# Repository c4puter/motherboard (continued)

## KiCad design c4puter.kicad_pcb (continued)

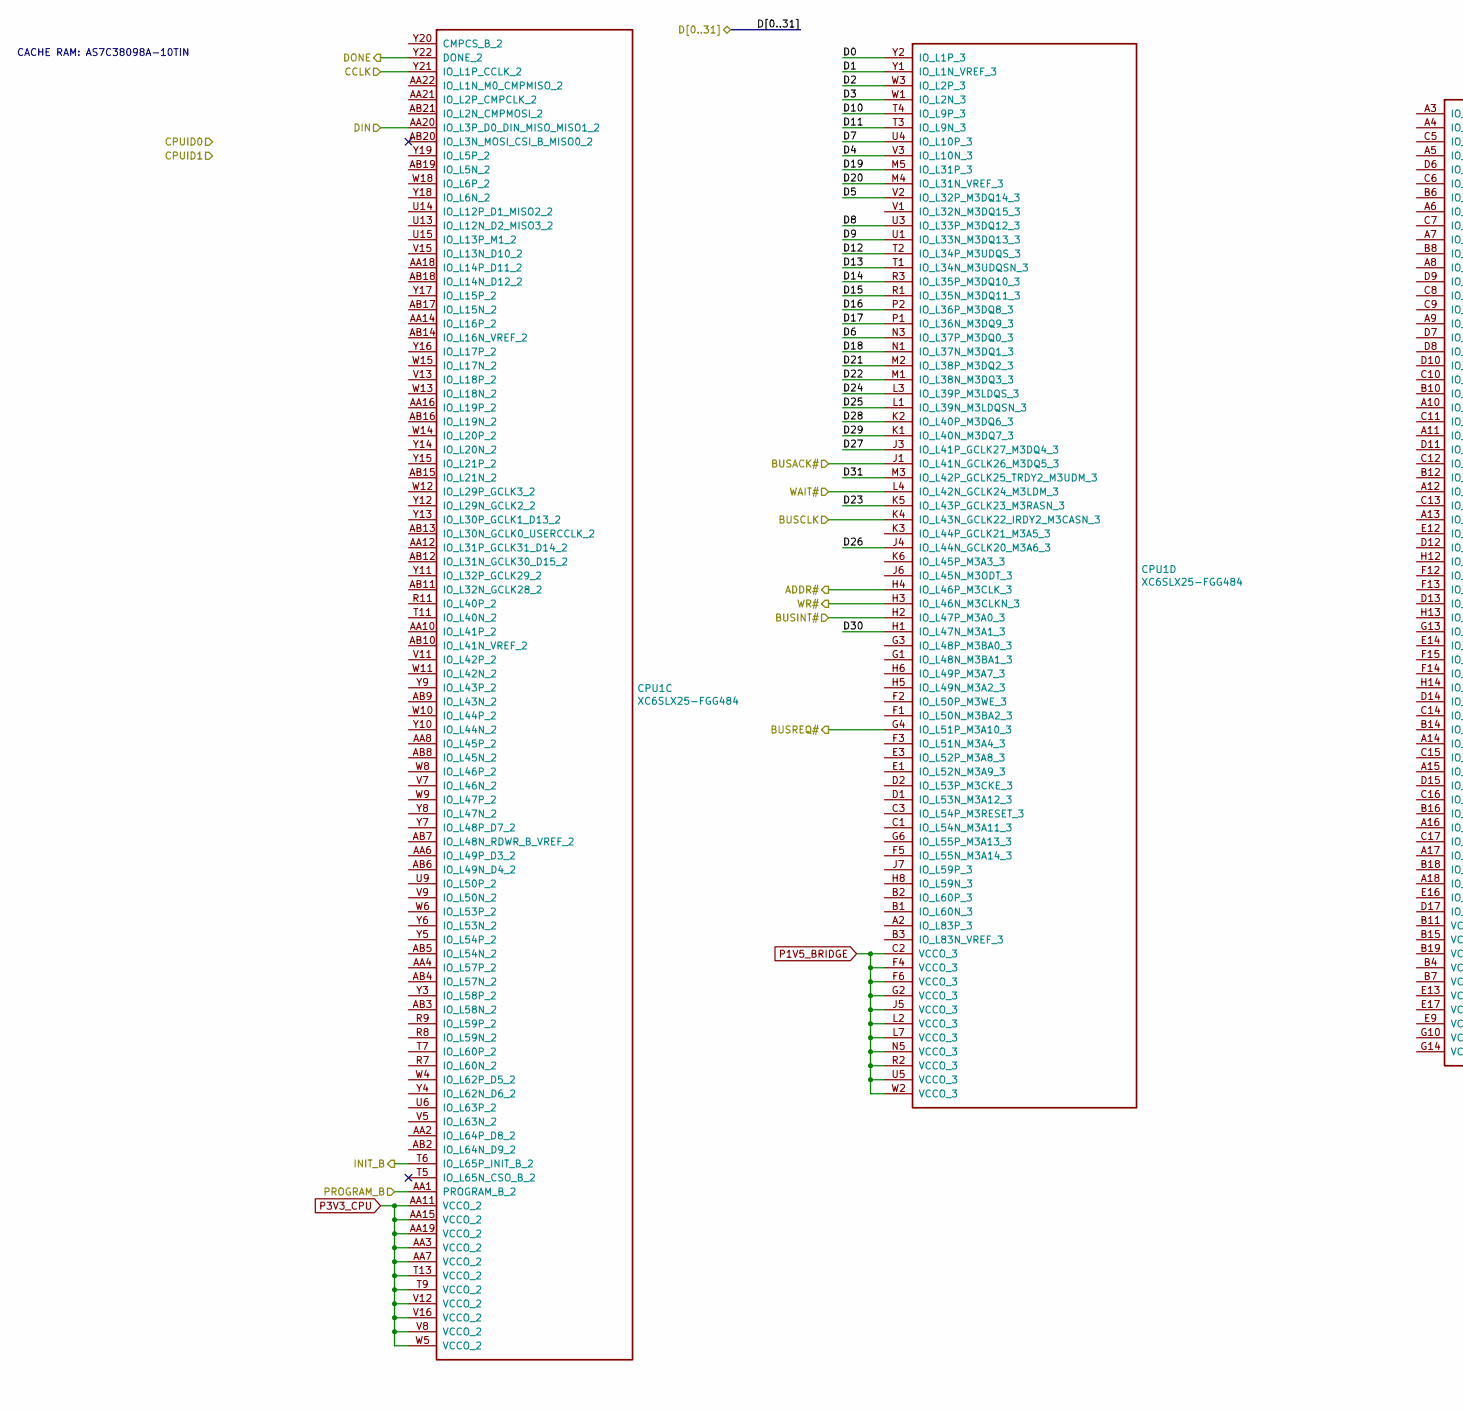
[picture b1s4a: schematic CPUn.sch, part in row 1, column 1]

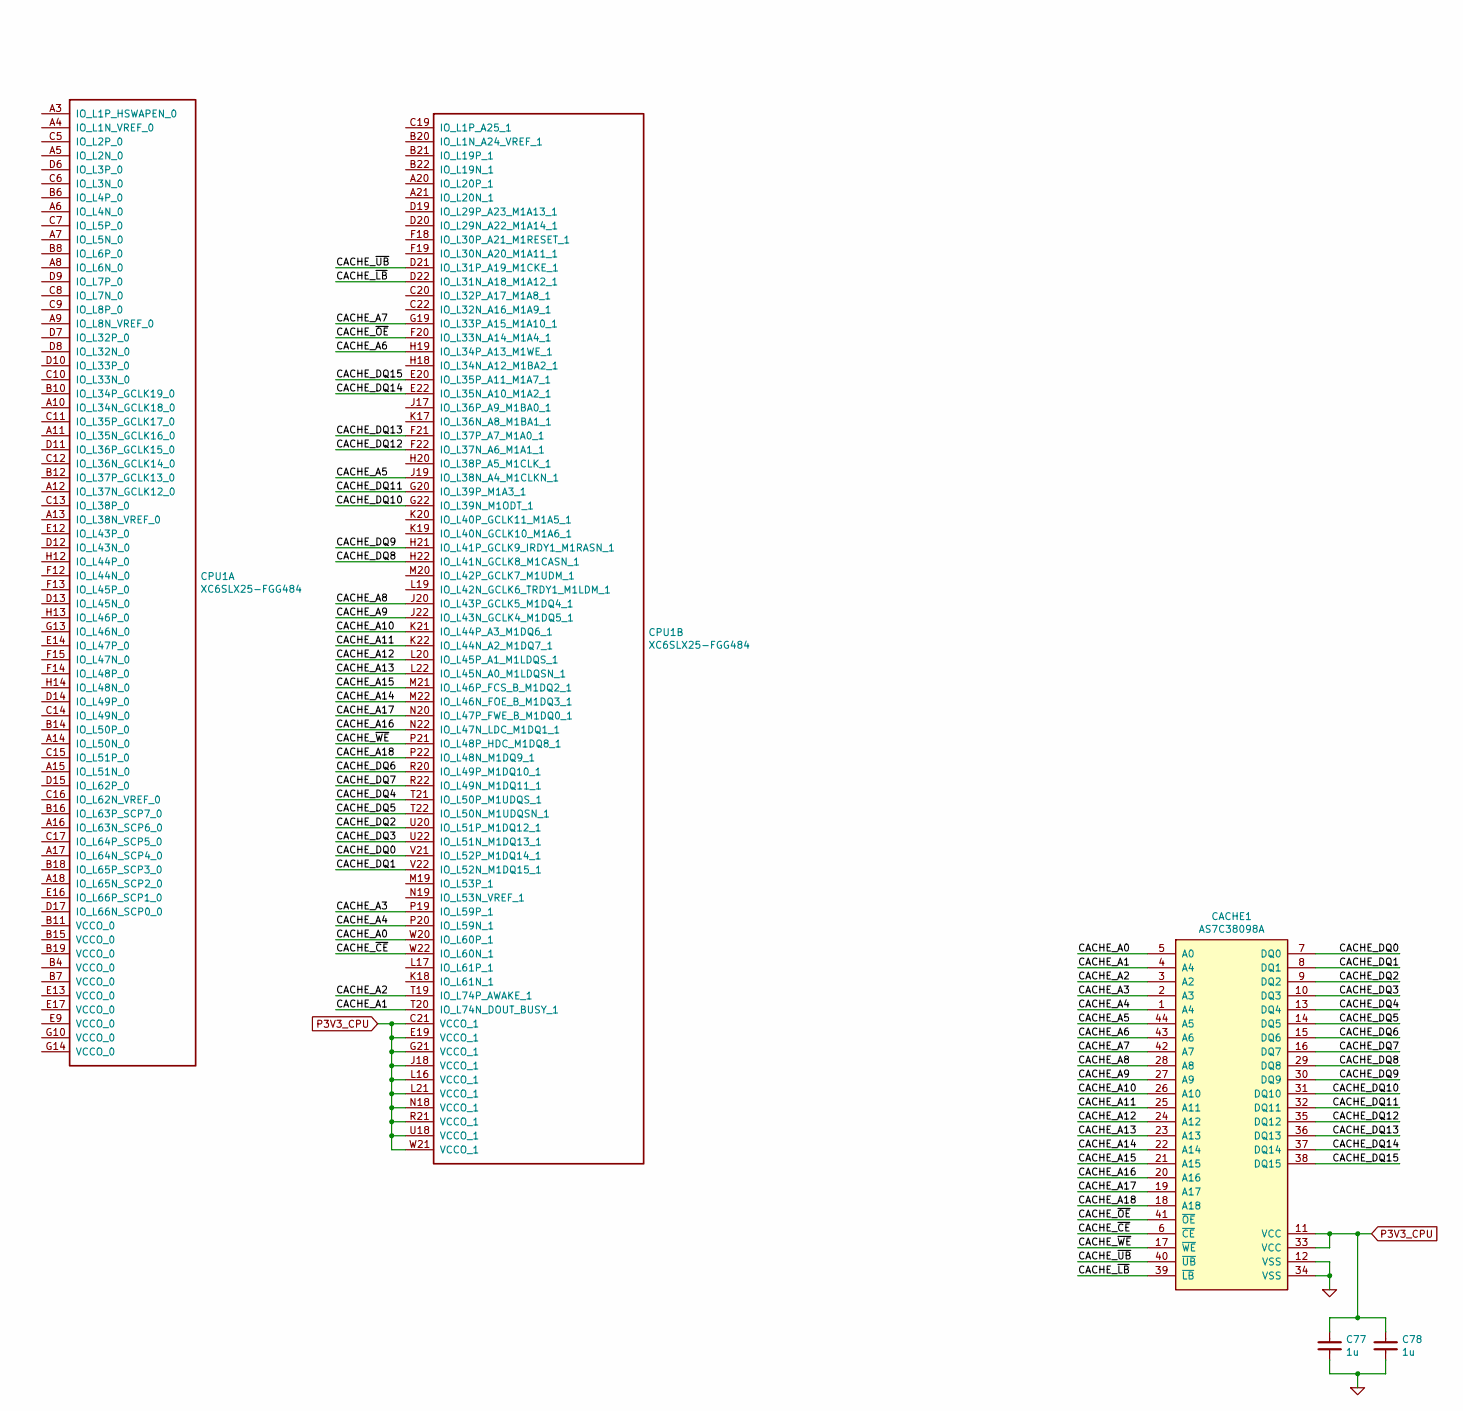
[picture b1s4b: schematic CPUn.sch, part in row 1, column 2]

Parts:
C75, C76: 1u; CAPC1005X55
CACHE0: AS7C38098A; SOP80P1176X120-44
CPU0: XC6SLX25-FGG484; XILINX-FGG484

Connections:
/CPU0/ADDR#: CPU0.H4 (IO_L46P_M3CLK_3); also elsewhere on the board
/CPU0/BUSACK#: CPU0.J1 (IO_L41N_GCLK26_M3DQ5_3); also elsewhere on the board
/CPU0/BUSCLK: CPU0.K4 (IO_L43N_GCLK22_IRDY2_M3CASN_3); also elsewhere on the board
/CPU0/BUSINT#: CPU0.H2 (IO_L47P_M3A0_3); also elsewhere on the board
/CPU0/BUSREQ#: CPU0.G4 (IO_L51P_M3A10_3); also elsewhere on the board
/CPU0/CACHE_A0: CACHE0.5 (A0), CPU0.W20 (IO_L60P_1)
/CPU0/CACHE_A1: CACHE0.4 (A4), CPU0.T20 (IO_L74N_DOUT_BUSY_1)
/CPU0/CACHE_A2: CACHE0.3 (A2), CPU0.T19 (IO_L74P_AWAKE_1)
/CPU0/CACHE_A3: CACHE0.2 (A3), CPU0.P19 (IO_L59P_1)
/CPU0/CACHE_A4: CACHE0.1 (A4), CPU0.P20 (IO_L59N_1)
/CPU0/CACHE_A5: CACHE0.44 (A5), CPU0.J19 (IO_L38N_A4_M1CLKN_1)
/CPU0/CACHE_A6: CACHE0.43 (A6), CPU0.H19 (IO_L34P_A13_M1WE_1)
/CPU0/CACHE_A7: CACHE0.42 (A7), CPU0.G19 (IO_L33P_A15_M1A10_1)
/CPU0/CACHE_A8: CACHE0.28 (A8), CPU0.J20 (IO_L43P_GCLK5_M1DQ4_1)
/CPU0/CACHE_A9: CACHE0.27 (A9), CPU0.J22 (IO_L43N_GCLK4_M1DQ5_1)
/CPU0/CACHE_A10: CACHE0.26 (A10), CPU0.K21 (IO_L44P_A3_M1DQ6_1)
/CPU0/CACHE_A11: CACHE0.25 (A11), CPU0.K22 (IO_L44N_A2_M1DQ7_1)
/CPU0/CACHE_A12: CACHE0.24 (A12), CPU0.L20 (IO_L45P_A1_M1LDQS_1)
/CPU0/CACHE_A13: CACHE0.23 (A13), CPU0.L22 (IO_L45N_A0_M1LDQSN_1)
/CPU0/CACHE_A14: CACHE0.22 (A14), CPU0.M22 (IO_L46N_FOE_B_M1DQ3_1)
/CPU0/CACHE_A15: CACHE0.21 (A15), CPU0.M21 (IO_L46P_FCS_B_M1DQ2_1)
/CPU0/CACHE_A16: CACHE0.20 (A16), CPU0.N22 (IO_L47N_LDC_M1DQ1_1)
/CPU0/CACHE_A17: CACHE0.19 (A17), CPU0.N20 (IO_L47P_FWE_B_M1DQ0_1)
/CPU0/CACHE_A18: CACHE0.18 (A18), CPU0.P22 (IO_L48N_M1DQ9_1)
/CPU0/CACHE_DQ0: CACHE0.7 (DQ0), CPU0.V21 (IO_L52P_M1DQ14_1)
/CPU0/CACHE_DQ1: CACHE0.8 (DQ1), CPU0.V22 (IO_L52N_M1DQ15_1)
/CPU0/CACHE_DQ2: CACHE0.9 (DQ2), CPU0.U20 (IO_L51P_M1DQ12_1)
/CPU0/CACHE_DQ3: CACHE0.10 (DQ3), CPU0.U22 (IO_L51N_M1DQ13_1)
/CPU0/CACHE_DQ4: CACHE0.13 (DQ4), CPU0.T21 (IO_L50P_M1UDQS_1)
/CPU0/CACHE_DQ5: CACHE0.14 (DQ5), CPU0.T22 (IO_L50N_M1UDQSN_1)
/CPU0/CACHE_DQ6: CACHE0.15 (DQ6), CPU0.R20 (IO_L49P_M1DQ10_1)
/CPU0/CACHE_DQ7: CACHE0.16 (DQ7), CPU0.R22 (IO_L49N_M1DQ11_1)
/CPU0/CACHE_DQ8: CACHE0.29 (DQ8), CPU0.H22 (IO_L41N_GCLK8_M1CASN_1)
/CPU0/CACHE_DQ9: CACHE0.30 (DQ9), CPU0.H21 (IO_L41P_GCLK9_IRDY1_M1RASN_1)
/CPU0/CACHE_DQ10: CACHE0.31 (DQ10), CPU0.G22 (IO_L39N_M1ODT_1)
/CPU0/CACHE_DQ11: CACHE0.32 (DQ11), CPU0.G20 (IO_L39P_M1A3_1)
/CPU0/CACHE_DQ12: CACHE0.35 (DQ12), CPU0.F22 (IO_L37N_A6_M1A1_1)
/CPU0/CACHE_DQ13: CACHE0.36 (DQ13), CPU0.F21 (IO_L37P_A7_M1A0_1)
/CPU0/CACHE_DQ14: CACHE0.37 (DQ14), CPU0.E22 (IO_L35N_A10_M1A2_1)
/CPU0/CACHE_DQ15: CACHE0.38 (DQ15), CPU0.E20 (IO_L35P_A11_M1A7_1)
/CPU0/CACHE_~CE: CACHE0.6 (~CE), CPU0.W22 (IO_L60N_1)
/CPU0/CACHE_~LB: CACHE0.39 (~LB), CPU0.D22 (IO_L31N_A18_M1A12_1)
/CPU0/CACHE_~OE: CACHE0.41 (~OE), CPU0.F20 (IO_L33N_A14_M1A4_1)
/CPU0/CACHE_~UB: CACHE0.40 (~UB), CPU0.D21 (IO_L31P_A19_M1CKE_1)
/CPU0/CACHE_~WE: CACHE0.17 (~WE), CPU0.P21 (IO_L48P_HDC_M1DQ8_1)
/CPU0/CCLK: CPU0.Y21 (IO_L1P_CCLK_2); also elsewhere on the board
/CPU0/DIN: CPU0.AA20 (IO_L3P_D0_DIN_MISO_MISO1_2); also elsewhere on the board
/CPU0/DONE: CPU0.Y22 (DONE_2); also elsewhere on the board
/CPU0/INIT_B: CPU0.T6 (IO_L65P_INIT_B_2); also elsewhere on the board
/CPU0/PROGRAM_B: CPU0.AA1 (PROGRAM_B_2); also elsewhere on the board
/Multibridge/CPU_D0: CPU0.Y2 (IO_L1P_3); also elsewhere on the board
/Multibridge/CPU_D1: CPU0.Y1 (IO_L1N_VREF_3); also elsewhere on the board
/Multibridge/CPU_D2: CPU0.W3 (IO_L2P_3); also elsewhere on the board
/Multibridge/CPU_D3: CPU0.W1 (IO_L2N_3); also elsewhere on the board
/Multibridge/CPU_D4: CPU0.V3 (IO_L10N_3); also elsewhere on the board
/Multibridge/CPU_D5: CPU0.V2 (IO_L32P_M3DQ14_3); also elsewhere on the board
/Multibridge/CPU_D6: CPU0.N3 (IO_L37P_M3DQ0_3); also elsewhere on the board
/Multibridge/CPU_D7: CPU0.U4 (IO_L10P_3); also elsewhere on the board
/Multibridge/CPU_D8: CPU0.U3 (IO_L33P_M3DQ12_3); also elsewhere on the board
/Multibridge/CPU_D9: CPU0.U1 (IO_L33N_M3DQ13_3); also elsewhere on the board
/Multibridge/CPU_D10: CPU0.T4 (IO_L9P_3); also elsewhere on the board
/Multibridge/CPU_D11: CPU0.T3 (IO_L9N_3); also elsewhere on the board
/Multibridge/CPU_D12: CPU0.T2 (IO_L34P_M3UDQS_3); also elsewhere on the board
/Multibridge/CPU_D13: CPU0.T1 (IO_L34N_M3UDQSN_3); also elsewhere on the board
/Multibridge/CPU_D14: CPU0.R3 (IO_L35P_M3DQ10_3); also elsewhere on the board
/Multibridge/CPU_D15: CPU0.R1 (IO_L35N_M3DQ11_3); also elsewhere on the board
/Multibridge/CPU_D16: CPU0.P2 (IO_L36P_M3DQ8_3); also elsewhere on the board
/Multibridge/CPU_D17: CPU0.P1 (IO_L36N_M3DQ9_3); also elsewhere on the board
/Multibridge/CPU_D18: CPU0.N1 (IO_L37N_M3DQ1_3); also elsewhere on the board
/Multibridge/CPU_D19: CPU0.M5 (IO_L31P_3); also elsewhere on the board
/Multibridge/CPU_D20: CPU0.M4 (IO_L31N_VREF_3); also elsewhere on the board
/Multibridge/CPU_D21: CPU0.M2 (IO_L38P_M3DQ2_3); also elsewhere on the board
/Multibridge/CPU_D22: CPU0.M1 (IO_L38N_M3DQ3_3); also elsewhere on the board
/Multibridge/CPU_D23: CPU0.K5 (IO_L43P_GCLK23_M3RASN_3); also elsewhere on the board
/Multibridge/CPU_D24: CPU0.L3 (IO_L39P_M3LDQS_3); also elsewhere on the board
/Multibridge/CPU_D25: CPU0.L1 (IO_L39N_M3LDQSN_3); also elsewhere on the board
/Multibridge/CPU_D26: CPU0.J4 (IO_L44N_GCLK20_M3A6_3); also elsewhere on the board
/Multibridge/CPU_D27: CPU0.J3 (IO_L41P_GCLK27_M3DQ4_3); also elsewhere on the board
/Multibridge/CPU_D28: CPU0.K2 (IO_L40P_M3DQ6_3); also elsewhere on the board
/Multibridge/CPU_D29: CPU0.K1 (IO_L40N_M3DQ7_3); also elsewhere on the board
/Multibridge/CPU_D30: CPU0.H1 (IO_L47N_M3A1_3); also elsewhere on the board
/Multibridge/CPU_D31: CPU0.M3 (IO_L42P_GCLK25_TRDY2_M3UDM_3); also elsewhere on the board
/Multibridge/CPU_WAIT#: CPU0.L4 (IO_L42N_GCLK24_M3LDM_3); also elsewhere on the board
/Multibridge/CPU_WR#: CPU0.H3 (IO_L46N_M3CLKN_3); also elsewhere on the board
GND: C75.2, C76.2, CACHE0.12 (VSS), CACHE0.34 (VSS); also elsewhere on the board
P1V5_BRIDGE: CPU0.C2 (VCCO_3), CPU0.F4 (VCCO_3), CPU0.F6 (VCCO_3), CPU0.G2 (VCCO_3), CPU0.J5 (VCCO_3), CPU0.L2 (VCCO_3), CPU0.L7 (VCCO_3), CPU0.N5 (VCCO_3), CPU0.R2 (VCCO_3), CPU0.U5 (VCCO_3), CPU0.W2 (VCCO_3); also elsewhere on the board
P3V3_CPU: C75.1, C76.1, CACHE0.11 (VCC), CACHE0.33 (VCC), CPU0.AA3 (VCCO_2), CPU0.AA7 (VCCO_2), CPU0.AA11 (VCCO_2), CPU0.AA15 (VCCO_2), CPU0.AA19 (VCCO_2), CPU0.C21 (VCCO_1), CPU0.E19 (VCCO_1), CPU0.G21 (VCCO_1), CPU0.J18 (VCCO_1), CPU0.L16 (VCCO_1), CPU0.L21 (VCCO_1), CPU0.N18 (VCCO_1), CPU0.R21 (VCCO_1), CPU0.T9 (VCCO_2), CPU0.T13 (VCCO_2), CPU0.U18 (VCCO_1), CPU0.V8 (VCCO_2), CPU0.V12 (VCCO_2), CPU0.V16 (VCCO_2), CPU0.W5 (VCCO_2), CPU0.W21 (VCCO_1); also elsewhere on the board

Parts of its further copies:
C77, C78: 1u; CAPC1005X55
CACHE1: AS7C38098A; SOP80P1176X120-44

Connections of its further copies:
/CPU1/CACHE_A0: CACHE1.5 (A0); also elsewhere on the board
/CPU1/CACHE_A1: CACHE1.4 (A4); also elsewhere on the board
/CPU1/CACHE_A2: CACHE1.3 (A2); also elsewhere on the board
/CPU1/CACHE_A3: CACHE1.2 (A3); also elsewhere on the board
/CPU1/CACHE_A4: CACHE1.1 (A4); also elsewhere on the board
/CPU1/CACHE_A5: CACHE1.44 (A5); also elsewhere on the board
/CPU1/CACHE_A6: CACHE1.43 (A6); also elsewhere on the board
/CPU1/CACHE_A7: CACHE1.42 (A7); also elsewhere on the board
/CPU1/CACHE_A8: CACHE1.28 (A8); also elsewhere on the board
/CPU1/CACHE_A9: CACHE1.27 (A9); also elsewhere on the board
/CPU1/CACHE_A10: CACHE1.26 (A10); also elsewhere on the board
/CPU1/CACHE_A11: CACHE1.25 (A11); also elsewhere on the board
/CPU1/CACHE_A12: CACHE1.24 (A12); also elsewhere on the board
/CPU1/CACHE_A13: CACHE1.23 (A13); also elsewhere on the board
/CPU1/CACHE_A14: CACHE1.22 (A14); also elsewhere on the board
/CPU1/CACHE_A15: CACHE1.21 (A15); also elsewhere on the board
/CPU1/CACHE_A16: CACHE1.20 (A16); also elsewhere on the board
/CPU1/CACHE_A17: CACHE1.19 (A17); also elsewhere on the board
/CPU1/CACHE_A18: CACHE1.18 (A18); also elsewhere on the board
/CPU1/CACHE_DQ0: CACHE1.7 (DQ0); also elsewhere on the board
/CPU1/CACHE_DQ1: CACHE1.8 (DQ1); also elsewhere on the board
/CPU1/CACHE_DQ2: CACHE1.9 (DQ2); also elsewhere on the board
/CPU1/CACHE_DQ3: CACHE1.10 (DQ3); also elsewhere on the board
/CPU1/CACHE_DQ4: CACHE1.13 (DQ4); also elsewhere on the board
/CPU1/CACHE_DQ5: CACHE1.14 (DQ5); also elsewhere on the board
/CPU1/CACHE_DQ6: CACHE1.15 (DQ6); also elsewhere on the board
/CPU1/CACHE_DQ7: CACHE1.16 (DQ7); also elsewhere on the board
/CPU1/CACHE_DQ8: CACHE1.29 (DQ8); also elsewhere on the board
/CPU1/CACHE_DQ9: CACHE1.30 (DQ9); also elsewhere on the board
/CPU1/CACHE_DQ10: CACHE1.31 (DQ10); also elsewhere on the board
/CPU1/CACHE_DQ11: CACHE1.32 (DQ11); also elsewhere on the board
/CPU1/CACHE_DQ12: CACHE1.35 (DQ12); also elsewhere on the board
/CPU1/CACHE_DQ13: CACHE1.36 (DQ13); also elsewhere on the board
/CPU1/CACHE_DQ14: CACHE1.37 (DQ14); also elsewhere on the board
/CPU1/CACHE_DQ15: CACHE1.38 (DQ15); also elsewhere on the board
/CPU1/CACHE_~CE: CACHE1.6 (~CE); also elsewhere on the board
/CPU1/CACHE_~LB: CACHE1.39 (~LB); also elsewhere on the board
/CPU1/CACHE_~OE: CACHE1.41 (~OE); also elsewhere on the board
/CPU1/CACHE_~UB: CACHE1.40 (~UB); also elsewhere on the board
/CPU1/CACHE_~WE: CACHE1.17 (~WE); also elsewhere on the board
GND: C77.2, C78.2, CACHE1.12 (VSS), CACHE1.34 (VSS); also elsewhere on the board
P3V3_CPU: C77.1, C78.1, CACHE1.11 (VCC), CACHE1.33 (VCC); also elsewhere on the board

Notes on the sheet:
CACHE RAM: AS7C38098A-10TIN

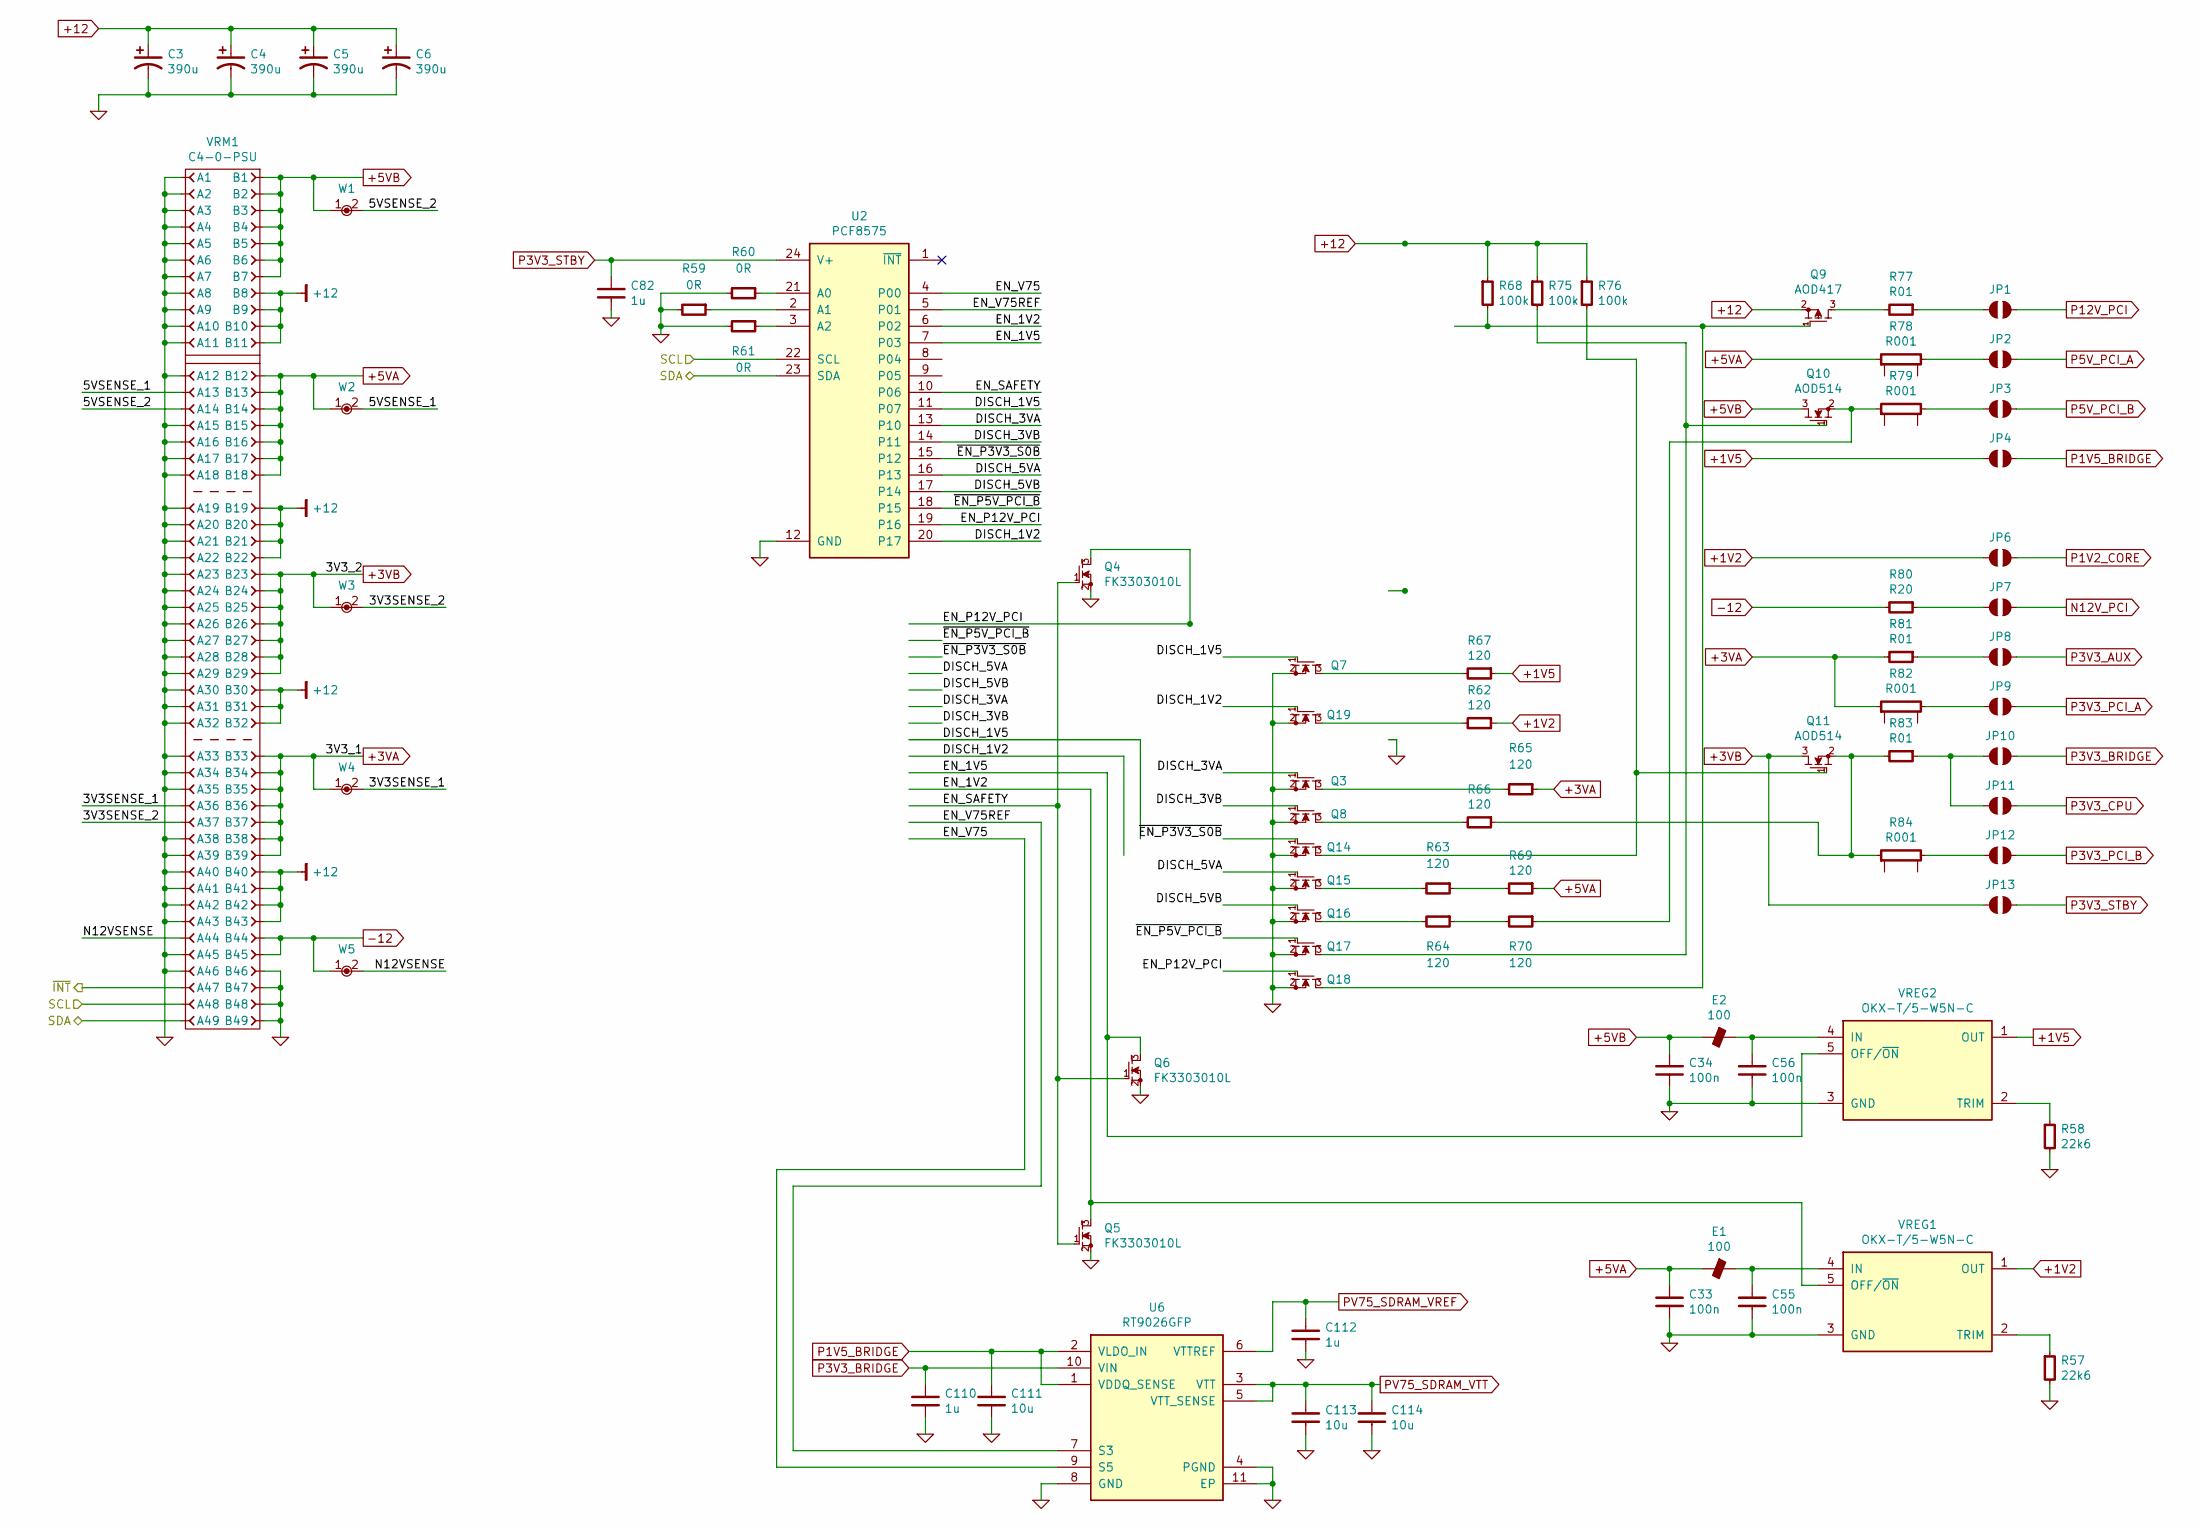
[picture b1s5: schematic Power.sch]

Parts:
C3, C4, C5, C6: 390u; C-ALUM-8mm
C33, C34, C55, C56: 100n; CAPC1005X55
C82, C110, C112: 1u; CAPC1005X55
C111, C113, C114: 10u; CAPC1608X55
E1, E2: 100; CAPC4532X220
JP1, JP2, JP3, JP4, JP6, JP7, JP8, JP9, JP10, JP11, JP12, JP13: JUMPER-SOLDER; JUMPER-SOLDER-SMD
Q3, Q4, Q5, Q6, Q7, Q8, Q14, Q15, Q16, Q17, Q18, Q19: FK3303010L; PANASONIC-SSSMini3-F2-B
Q9: AOD417; TO-252
Q10, Q11: AOD514; TO-252
R57, R58: 22k6; RESC1608X50
R59, R60, R61: 0R; RESC1005X40
R62, R63, R64, R65, R66, R67, R69, R70: 120; RESC1608X50
R68, R75, R76: 100k; RESC1005X40
R77, R81, R83: R01; RESC2012X50
R78, R79, R82, R84: R001; VISHAY-WSL3637-LARGE
R80: R20; RESC2012X50
U2: PCF8575; SOP65P775X200-24
U6: RT9026GFP; SOP50P490X110-11
VREG1, VREG2: OKX-T/5-W5N-C; MURATA-OKX-T5-W5
VRM1: C4-0-PSU; CONN-10018783-10202TLF-PCIEx8-FCI
W1, W2, W3, W4, W5: NET-TIE; NET-TIE-0.2mm

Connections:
+1V2: JP6.1, R62.1, VREG1.1 (OUT)
+1V5: JP4.1, R67.1, VREG2.1 (OUT)
+3VA: R65.1, R81.2, R82.1, VRM1.B33, VRM1.B34, VRM1.B35, VRM1.B36, VRM1.B37, VRM1.B38, VRM1.B39, W4.1
+3VB: JP13.1, Q11.3 (D), VRM1.B23, VRM1.B24, VRM1.B25, VRM1.B26, VRM1.B27, VRM1.B28, VRM1.B29, W3.1
+5VA: C33.1, E1.1, R69.1, R78.1, VRM1.B12, VRM1.B13, VRM1.B14, VRM1.B15, VRM1.B16, VRM1.B17, VRM1.B18, W2.1
+5VB: C34.1, E2.1, Q10.3 (D), VRM1.B1, VRM1.B2, VRM1.B3, VRM1.B4, VRM1.B5, VRM1.B6, VRM1.B7, W1.1
+12: C3.1, C4.1, C5.1, C6.1, Q9.2 (S), R68.1, R75.1, R76.1, VRM1.B8, VRM1.B9, VRM1.B10, VRM1.B11, VRM1.B19, VRM1.B20, VRM1.B21, VRM1.B22, VRM1.B30, VRM1.B31, VRM1.B32, VRM1.B40, VRM1.B41, VRM1.B42, VRM1.B43; also elsewhere on the board
-12: R80.2, VRM1.B44, VRM1.B45, W5.1
/Blinkenlights/SCL: U2.22 (SCL), VRM1.A48; also elsewhere on the board
/Blinkenlights/SDA: U2.23 (SDA), VRM1.A49; also elsewhere on the board
/Power/3V3SENSE_1: VRM1.A36, W4.2
/Power/3V3SENSE_2: VRM1.A37, W3.2
/Power/5VSENSE_1: VRM1.A13, W2.2
/Power/5VSENSE_2: VRM1.A14, W1.2
/Power/DISCH_1V2: Q19.1, U2.20 (P17)
/Power/DISCH_1V5: Q7.1, U2.11 (P07)
/Power/DISCH_3VA: Q3.1, U2.13 (P10)
/Power/DISCH_3VB: Q8.1, U2.14 (P11)
/Power/DISCH_5VA: Q15.1, U2.16 (P13)
/Power/DISCH_5VB: Q16.1, U2.17 (P14)
/Power/EN_1V2: Q5.3, U2.6 (P02), VREG1.5 (OFF/~ON)
/Power/EN_1V5: Q6.3, U2.7 (P03), VREG2.5 (OFF/~ON)
/Power/EN_P12V_PCI: Q4.3, Q18.1, U2.19 (P16)
/Power/EN_SAFETY: Q4.1, Q5.1, Q6.1, U2.10 (P06)
/Power/EN_V75: U2.4 (P00), U6.9 (S5)
/Power/EN_V75REF: U2.5 (P01), U6.7 (S3)
/Power/N12VSENSE: VRM1.A44, W5.2
/Power/~EN_P3V3_S0B: Q14.1, U2.15 (P12)
/Power/~EN_P5V_PCI_B: Q17.1, U2.18 (P15)
/Power/~INT: VRM1.A47
GND: C3.2, C4.2, C5.2, C6.2, C33.2, C34.2, C55.2, C56.2, C82.2, C110.2, C111.2, C112.2, C113.2, C114.2, Q3.2, Q4.2, Q5.2, Q6.2, Q7.2, Q8.2, Q14.2, Q15.2, Q16.2, Q17.2, Q18.2, Q19.2, R57.2, R58.2, R59.2, R60.2, R61.2, U2.12 (GND), U6.4 (PGND), U6.8 (GND), U6.11 (EP), VREG1.3 (GND), VREG2.3 (GND), VRM1.A1, VRM1.A2, VRM1.A3, VRM1.A4, VRM1.A5, VRM1.A6, VRM1.A7, VRM1.A8, VRM1.A9, VRM1.A10, VRM1.A11, VRM1.A12, VRM1.A15, VRM1.A16, VRM1.A17, VRM1.A18, VRM1.A19, VRM1.A20, VRM1.A21, VRM1.A22, VRM1.A23, VRM1.A24, VRM1.A25, VRM1.A26, VRM1.A27, VRM1.A28, VRM1.A29, VRM1.A30, VRM1.A31, VRM1.A32, VRM1.A33, VRM1.A34, VRM1.A35, VRM1.A38, VRM1.A39, VRM1.A40, VRM1.A41, VRM1.A42, VRM1.A43, VRM1.A45, VRM1.A46, VRM1.B46, VRM1.B47, VRM1.B48, VRM1.B49; also elsewhere on the board
N12V_PCI: JP7.2; also elsewhere on the board
unnamed: C55.1, E1.2, VREG1.4 (IN)
unnamed: C56.1, E2.2, VREG2.4 (IN)
unnamed: JP1.1, R77.1
unnamed: JP2.1, R78.4
unnamed: JP3.1, R79.4
unnamed: JP7.1, R80.1
unnamed: JP8.1, R81.1
unnamed: JP9.1, R82.4
unnamed: JP10.1, JP11.1, R83.1
unnamed: JP12.1, R84.4
unnamed: Q3.3, R65.2
unnamed: Q7.3, R67.2
unnamed: Q8.3, R66.2
unnamed: Q9.3 (D), R77.2
unnamed: Q10.1 (G), Q17.3, R75.2
unnamed: Q10.2 (S), R70.1, R79.1
unnamed: Q11.1 (G), Q14.3, R76.2
unnamed: Q11.2 (S), R66.1, R83.2, R84.1
unnamed: Q15.3, R63.2
unnamed: Q16.3, R64.2
unnamed: Q9.1 (G), Q18.3, R68.2
unnamed: Q19.3, R62.2
unnamed: R57.1, VREG1.2 (TRIM)
unnamed: R58.1, VREG2.2 (TRIM)
unnamed: R59.1, U2.2 (A1)
unnamed: R60.1, U2.21 (A0)
unnamed: R61.1, U2.3 (A2)
unnamed: R63.1, R69.2
unnamed: R64.1, R70.2
P1V2_CORE: JP6.2; also elsewhere on the board
P1V5_BRIDGE: C111.1, JP4.2, U6.1 (VDDQ_SENSE), U6.2 (VLDO_IN); also elsewhere on the board
P3V3_AUX: JP8.2; also elsewhere on the board
P3V3_BRIDGE: C110.1, JP10.2, U6.10 (VIN); also elsewhere on the board
P3V3_CPU: JP11.2; also elsewhere on the board
P3V3_PCI_A: JP9.2; also elsewhere on the board
P3V3_PCI_B: JP12.2; also elsewhere on the board
P3V3_STBY: C82.1, JP13.2, U2.24 (V+); also elsewhere on the board
P5V_PCI_A: JP2.2; also elsewhere on the board
P5V_PCI_B: JP3.2; also elsewhere on the board
P12V_PCI: JP1.2; also elsewhere on the board
PV75_SDRAM_VREF: C112.1, U6.6 (VTTREF); also elsewhere on the board
PV75_SDRAM_VTT: C113.1, C114.1, U6.3 (VTT), U6.5 (VTT_SENSE); also elsewhere on the board

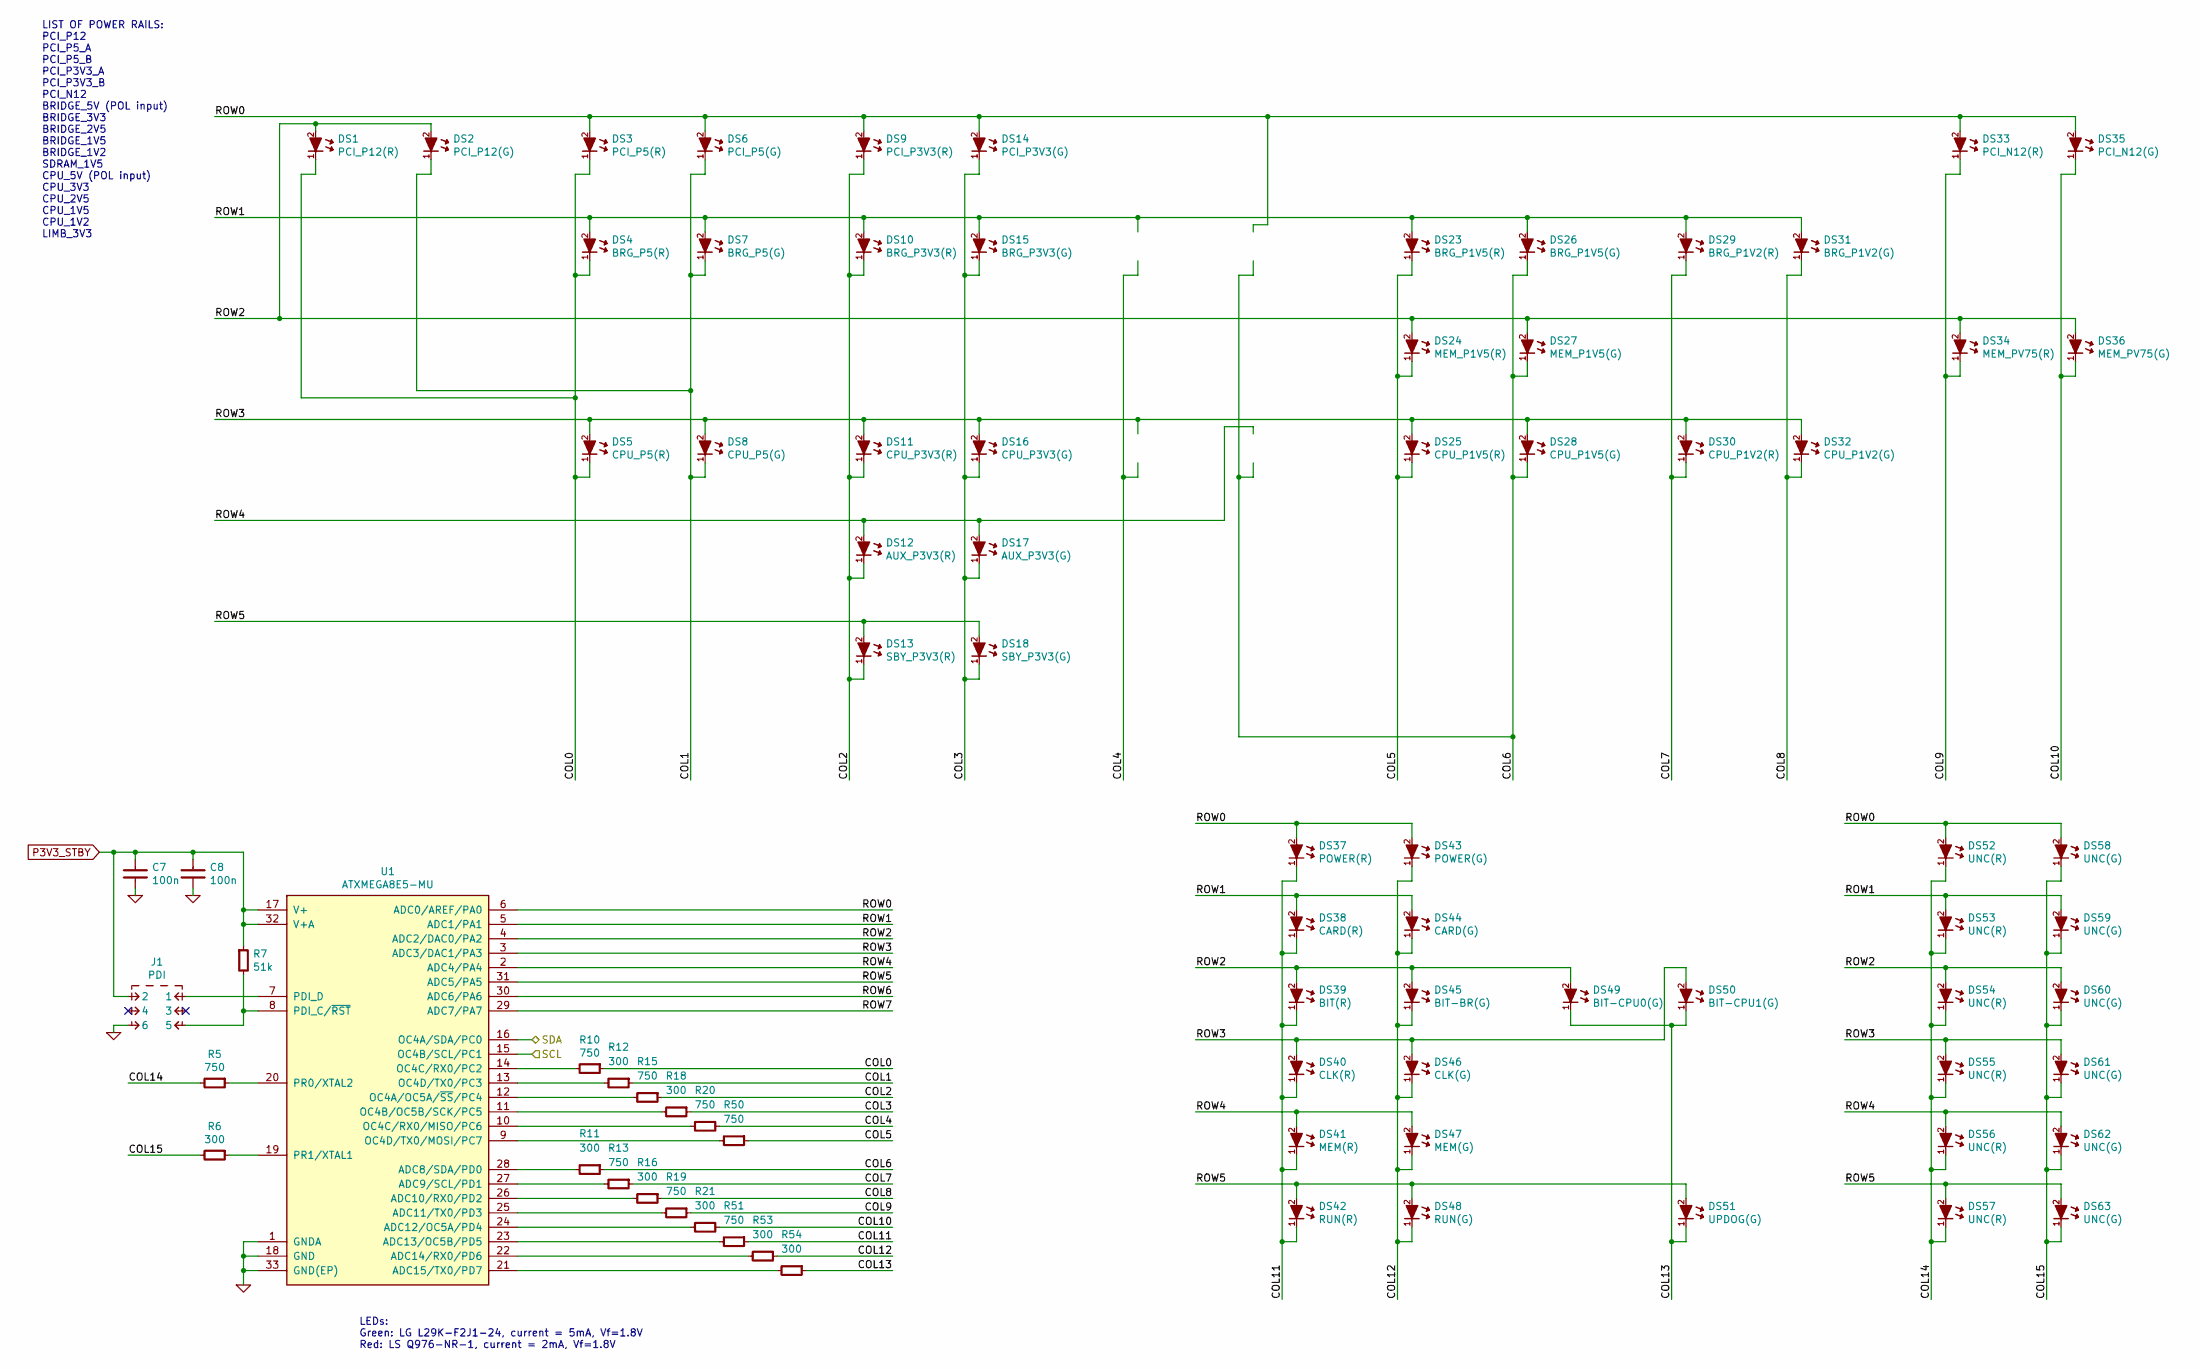
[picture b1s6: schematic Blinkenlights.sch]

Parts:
C7, C8: 100n; CAPC1005X55
DS1: PCI_P12(R); LED-0603
DS2: PCI_P12(G); LED-0603
DS3: PCI_P5(R); LED-0603
DS4: BRG_P5(R); LED-0603
DS5: CPU_P5(R); LED-0603
DS6: PCI_P5(G); LED-0603
DS7: BRG_P5(G); LED-0603
DS8: CPU_P5(G); LED-0603
DS9: PCI_P3V3(R); LED-0603
DS10: BRG_P3V3(R); LED-0603
DS11: CPU_P3V3(R); LED-0603
DS12: AUX_P3V3(R); LED-0603
DS13: SBY_P3V3(R); LED-0603
DS14: PCI_P3V3(G); LED-0603
DS15: BRG_P3V3(G); LED-0603
DS16: CPU_P3V3(G); LED-0603
DS17: AUX_P3V3(G); LED-0603
DS18: SBY_P3V3(G); LED-0603
DS23: BRG_P1V5(R); LED-0603
DS24: MEM_P1V5(R); LED-0603
DS25: CPU_P1V5(R); LED-0603
DS26: BRG_P1V5(G); LED-0603
DS27: MEM_P1V5(G); LED-0603
DS28: CPU_P1V5(G); LED-0603
DS29: BRG_P1V2(R); LED-0603
DS30: CPU_P1V2(R); LED-0603
DS31: BRG_P1V2(G); LED-0603
DS32: CPU_P1V2(G); LED-0603
DS33: PCI_N12(R); LED-0603
DS34: MEM_PV75(R); LED-0603
DS35: PCI_N12(G); LED-0603
DS36: MEM_PV75(G); LED-0603
DS37: POWER(R); LED-0603
DS38: CARD(R); LED-0603
DS39: BIT(R); LED-0603
DS40: CLK(R); LED-0603
DS41: MEM(R); LED-0603
DS42: RUN(R); LED-0603
DS43: POWER(G); LED-0603
DS44: CARD(G); LED-0603
DS45: BIT-BR(G); LED-0603
DS46: CLK(G); LED-0603
DS47: MEM(G); LED-0603
DS48: RUN(G); LED-0603
DS49: BIT-CPU0(G); LED-0603
DS50: BIT-CPU1(G); LED-0603
DS51: UPDOG(G); LED-0603
DS52, DS53, DS54, DS55, DS56, DS57: UNC(R); LED-0603
DS58, DS59, DS60, DS61, DS62, DS63: UNC(G); LED-0603
J1: PDI; CONN-100MIL-M-2x3
R5, R10, R13, R15, R19, R20, R50, R51: 750; RESC1608X50
R6, R11, R12, R16, R18, R21, R53, R54: 300; RESC1608X50
R7: 51k; RESC1608X50
U1: ATXMEGA8E5-MU; QFN50P500X500X100-33

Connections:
/Blinkenlights/COL0: DS1.1 (K), DS3.1 (K), DS4.1 (K), DS5.1 (K), R10.1
/Blinkenlights/COL1: DS2.1 (K), DS6.1 (K), DS7.1 (K), DS8.1 (K), R12.1
/Blinkenlights/COL2: DS9.1 (K), DS10.1 (K), DS11.1 (K), DS12.1 (K), DS13.1 (K), R15.1
/Blinkenlights/COL3: DS14.1 (K), DS15.1 (K), DS16.1 (K), DS17.1 (K), DS18.1 (K), R18.1
/Blinkenlights/COL4: R20.1
/Blinkenlights/COL5: DS23.1 (K), DS24.1 (K), DS25.1 (K), R50.1
/Blinkenlights/COL6: DS26.1 (K), DS27.1 (K), DS28.1 (K), R11.1
/Blinkenlights/COL7: DS29.1 (K), DS30.1 (K), R13.1
/Blinkenlights/COL8: DS31.1 (K), DS32.1 (K), R16.1
/Blinkenlights/COL9: DS33.1 (K), DS34.1 (K), R19.1
/Blinkenlights/COL10: DS35.1 (K), DS36.1 (K), R21.1
/Blinkenlights/COL11: DS37.1 (K), DS38.1 (K), DS39.1 (K), DS40.1 (K), DS41.1 (K), DS42.1 (K), R51.1
/Blinkenlights/COL12: DS43.1 (K), DS44.1 (K), DS45.1 (K), DS46.1 (K), DS47.1 (K), DS48.1 (K), R53.1
/Blinkenlights/COL13: DS49.1 (K), DS50.1 (K), DS51.1 (K), R54.1
/Blinkenlights/COL14: DS52.1 (K), DS53.1 (K), DS54.1 (K), DS55.1 (K), DS56.1 (K), DS57.1 (K), R5.2
/Blinkenlights/COL15: DS58.1 (K), DS59.1 (K), DS60.1 (K), DS61.1 (K), DS62.1 (K), DS63.1 (K), R6.2
/Blinkenlights/ROW0: DS3.2 (A), DS6.2 (A), DS9.2 (A), DS14.2 (A), DS33.2 (A), DS35.2 (A), DS37.2 (A), DS43.2 (A), DS52.2 (A), DS58.2 (A), U1.6 (ADC0/AREF/PA0)
/Blinkenlights/ROW1: DS4.2 (A), DS7.2 (A), DS10.2 (A), DS15.2 (A), DS23.2 (A), DS26.2 (A), DS29.2 (A), DS31.2 (A), DS38.2 (A), DS44.2 (A), DS53.2 (A), DS59.2 (A), U1.5 (ADC1/PA1)
/Blinkenlights/ROW2: DS1.2 (A), DS2.2 (A), DS24.2 (A), DS27.2 (A), DS34.2 (A), DS36.2 (A), DS39.2 (A), DS45.2 (A), DS49.2 (A), DS54.2 (A), DS60.2 (A), U1.4 (ADC2/DAC0/PA2)
/Blinkenlights/ROW3: DS5.2 (A), DS8.2 (A), DS11.2 (A), DS16.2 (A), DS25.2 (A), DS28.2 (A), DS30.2 (A), DS32.2 (A), DS40.2 (A), DS46.2 (A), DS50.2 (A), DS55.2 (A), DS61.2 (A), U1.3 (ADC3/DAC1/PA3)
/Blinkenlights/ROW4: DS12.2 (A), DS17.2 (A), DS41.2 (A), DS47.2 (A), DS56.2 (A), DS62.2 (A), U1.2 (ADC4/PA4)
/Blinkenlights/ROW5: DS13.2 (A), DS18.2 (A), DS42.2 (A), DS48.2 (A), DS51.2 (A), DS57.2 (A), DS63.2 (A), U1.31 (ADC5/PA5)
/Blinkenlights/ROW6: U1.30 (ADC6/PA6)
/Blinkenlights/ROW7: U1.29 (ADC7/PA7)
/Blinkenlights/SCL: U1.15 (OC4B/SCL/PC1); also elsewhere on the board
/Blinkenlights/SDA: U1.16 (OC4A/SDA/PC0); also elsewhere on the board
GND: C7.1, C8.1, J1.6, U1.1 (GNDA), U1.18 (GND), U1.33 (GND(EP)); also elsewhere on the board
unnamed: J1.1, U1.7 (PDI_D)
unnamed: J1.5, R7.2, U1.8 (PDI_C/~RST)
unnamed: R5.1, U1.20 (PR0/XTAL2)
unnamed: R6.1, U1.19 (PR1/XTAL1)
unnamed: R10.2, U1.14 (OC4C/RX0/PC2)
unnamed: R11.2, U1.28 (ADC8/SDA/PD0)
unnamed: R12.2, U1.13 (OC4D/TX0/PC3)
unnamed: R13.2, U1.27 (ADC9/SCL/PD1)
unnamed: R15.2, U1.12 (OC4A/OC5A/~SS~/PC4)
unnamed: R16.2, U1.26 (ADC10/RX0/PD2)
unnamed: R18.2, U1.11 (OC4B/OC5B/SCK/PC5)
unnamed: R19.2, U1.25 (ADC11/TX0/PD3)
unnamed: R20.2, U1.10 (OC4C/RX0/MISO/PC6)
unnamed: R21.2, U1.24 (ADC12/OC5A/PD4)
unnamed: R50.2, U1.9 (OC4D/TX0/MOSI/PC7)
unnamed: R51.2, U1.23 (ADC13/OC5B/PD5)
unnamed: R53.2, U1.22 (ADC14/RX0/PD6)
unnamed: R54.2, U1.21 (ADC15/TX0/PD7)
P3V3_STBY: C7.2, C8.2, J1.2, R7.1, U1.17 (V+), U1.32 (V+A); also elsewhere on the board

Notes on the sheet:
LIST OF POWER RAILS: PCI_P12 PCI_P5_A PCI_P5_B PCI_P3V3_A PCI_P3V3_B PCI_N12 BRIDGE_5V (POL input) BRIDGE_3V3 BRIDGE_2V5 BRIDGE_1V5 BRIDGE_1V2 SDRAM_1V5 CPU_5V (POL input) CPU_3V3 CPU_2V5 CPU_1V5 CPU_1V2 LIMB_3V3
LEDs: Green: LG L29K-F2J1-24, current = 5mA, Vf=1.8V Red: LS Q976-NR-1, current = 2mA, Vf=1.8V
